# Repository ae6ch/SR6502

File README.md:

# SR6502
Ben Eater style 6502 SBC

Memory Map:  (eventually going to move to a FPGA for mapping)
$0000-$7FFF 32K SRAM (minus 256 Bytes for IO)

$7F00-$7FFF IO

 $7F00 VIA1

 $7F10 ACIA1

$8000-$FFFF 32K EEPROM

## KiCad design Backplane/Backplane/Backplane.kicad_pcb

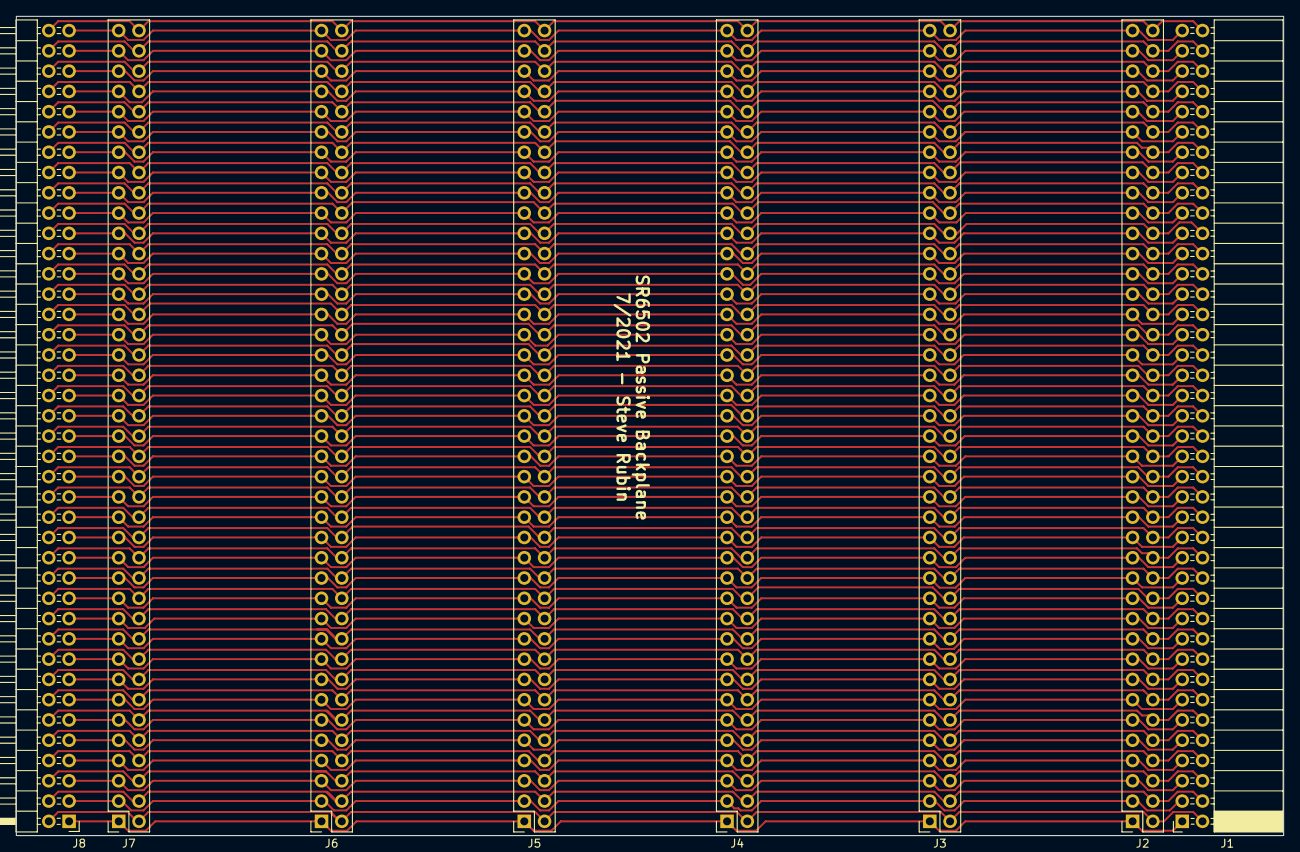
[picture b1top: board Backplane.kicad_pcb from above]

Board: 2 copper layers, 158.8 x 102.6 mm, 8 parts (0 on the bottom side), 80 nets.

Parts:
J1: Conn_02x40_Counter_Clockwise; PinSocket_2x40_P2.54mm_Horizontal
J2, J3, J4, J5, J6, J7: Conn_02x40_Counter_Clockwise; PinSocket_2x40_P2.54mm_Vertical
J8: Conn_02x40_Counter_Clockwise; PinHeader_2x40_P2.54mm_Horizontal

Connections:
/1: J1.1, J2.1, J3.1, J4.1, J5.1, J6.1, J7.1, J8.1
/2: J1.3, J2.3, J3.3, J4.3, J5.3, J6.3, J7.3, J8.3
/3: J1.5, J2.5, J3.5, J4.5, J5.5, J6.5, J7.5, J8.5
/4: J1.7, J2.7, J3.7, J4.7, J5.7, J6.7, J7.7, J8.7
/5: J1.9, J2.9, J3.9, J4.9, J5.9, J6.9, J7.9, J8.9
/6: J1.11, J2.11, J3.11, J4.11, J5.11, J6.11, J7.11, J8.11
/7: J1.13, J2.13, J3.13, J4.13, J5.13, J6.13, J7.13, J8.13
/8: J1.15, J2.15, J3.15, J4.15, J5.15, J6.15, J7.15, J8.15
/9: J1.17, J2.17, J3.17, J4.17, J5.17, J6.17, J7.17, J8.17
/10: J1.19, J2.19, J3.19, J4.19, J5.19, J6.19, J7.19, J8.19
/11: J1.21, J2.21, J3.21, J4.21, J5.21, J6.21, J7.21, J8.21
/12: J1.23, J2.23, J3.23, J4.23, J5.23, J6.23, J7.23, J8.23
/13: J1.25, J2.25, J3.25, J4.25, J5.25, J6.25, J7.25, J8.25
/14: J1.27, J2.27, J3.27, J4.27, J5.27, J6.27, J7.27, J8.27
/15: J1.29, J2.29, J3.29, J4.29, J5.29, J6.29, J7.29, J8.29
/16: J1.31, J2.31, J3.31, J4.31, J5.31, J6.31, J7.31, J8.31
/17: J1.33, J2.33, J3.33, J4.33, J5.33, J6.33, J7.33, J8.33
/18: J1.35, J2.35, J3.35, J4.35, J5.35, J6.35, J7.35, J8.35
/19: J1.37, J2.37, J3.37, J4.37, J5.37, J6.37, J7.37, J8.37
/20: J1.39, J2.39, J3.39, J4.39, J5.39, J6.39, J7.39, J8.39
/21: J1.41, J2.41, J3.41, J4.41, J5.41, J6.41, J7.41, J8.41
/22: J1.43, J2.43, J3.43, J4.43, J5.43, J6.43, J7.43, J8.43
/23: J1.45, J2.45, J3.45, J4.45, J5.45, J6.45, J7.45, J8.45
/24: J1.47, J2.47, J3.47, J4.47, J5.47, J6.47, J7.47, J8.47
/25: J1.49, J2.49, J3.49, J4.49, J5.49, J6.49, J7.49, J8.49
/26: J1.51, J2.51, J3.51, J4.51, J5.51, J6.51, J7.51, J8.51
/27: J1.53, J2.53, J3.53, J4.53, J5.53, J6.53, J7.53, J8.53
/28: J1.55, J2.55, J3.55, J4.55, J5.55, J6.55, J7.55, J8.55
/29: J1.57, J2.57, J3.57, J4.57, J5.57, J6.57, J7.57, J8.57
/30: J1.59, J2.59, J3.59, J4.59, J5.59, J6.59, J7.59, J8.59
/31: J1.61, J2.61, J3.61, J4.61, J5.61, J6.61, J7.61, J8.61
/32: J1.63, J2.63, J3.63, J4.63, J5.63, J6.63, J7.63, J8.63
/33: J1.65, J2.65, J3.65, J4.65, J5.65, J6.65, J7.65, J8.65
/34: J1.67, J2.67, J3.67, J4.67, J5.67, J6.67, J7.67, J8.67
/35: J1.69, J2.69, J3.69, J4.69, J5.69, J6.69, J7.69, J8.69
/36: J1.71, J2.71, J3.71, J4.71, J5.71, J6.71, J7.71, J8.71
/37: J1.73, J2.73, J3.73, J4.73, J5.73, J6.73, J7.73, J8.73
/38: J1.75, J2.75, J3.75, J4.75, J5.75, J6.75, J7.75, J8.75
/39: J1.77, J2.77, J3.77, J4.77, J5.77, J6.77, J7.77, J8.77
/40: J1.79, J2.79, J3.79, J4.79, J5.79, J6.79, J7.79, J8.79
/41: J1.80, J2.80, J3.80, J4.80, J5.80, J6.80, J7.80, J8.80
/42: J1.78, J2.78, J3.78, J4.78, J5.78, J6.78, J7.78, J8.78
/43: J1.76, J2.76, J3.76, J4.76, J5.76, J6.76, J7.76, J8.76
/44: J1.74, J2.74, J3.74, J4.74, J5.74, J6.74, J7.74, J8.74
/45: J1.72, J2.72, J3.72, J4.72, J5.72, J6.72, J7.72, J8.72
/46: J1.70, J2.70, J3.70, J4.70, J5.70, J6.70, J7.70, J8.70
/47: J1.68, J2.68, J3.68, J4.68, J5.68, J6.68, J7.68, J8.68
/48: J1.66, J2.66, J3.66, J4.66, J5.66, J6.66, J7.66, J8.66
/49: J1.64, J2.64, J3.64, J4.64, J5.64, J6.64, J7.64, J8.64
/50: J1.62, J2.62, J3.62, J4.62, J5.62, J6.62, J7.62, J8.62
/51: J1.60, J2.60, J3.60, J4.60, J5.60, J6.60, J7.60, J8.60
/52: J1.58, J2.58, J3.58, J4.58, J5.58, J6.58, J7.58, J8.58
/53: J1.56, J2.56, J3.56, J4.56, J5.56, J6.56, J7.56, J8.56
/54: J1.54, J2.54, J3.54, J4.54, J5.54, J6.54, J7.54, J8.54
/55: J1.52, J2.52, J3.52, J4.52, J5.52, J6.52, J7.52, J8.52
/56: J1.50, J2.50, J3.50, J4.50, J5.50, J6.50, J7.50, J8.50
/57: J1.48, J2.48, J3.48, J4.48, J5.48, J6.48, J7.48, J8.48
/58: J1.46, J2.46, J3.46, J4.46, J5.46, J6.46, J7.46, J8.46
/59: J1.44, J2.44, J3.44, J4.44, J5.44, J6.44, J7.44, J8.44
/60: J1.42, J2.42, J3.42, J4.42, J5.42, J6.42, J7.42, J8.42
/61: J1.40, J2.40, J3.40, J4.40, J5.40, J6.40, J7.40, J8.40
/62: J1.38, J2.38, J3.38, J4.38, J5.38, J6.38, J7.38, J8.38
/63: J1.36, J2.36, J3.36, J4.36, J5.36, J6.36, J7.36, J8.36
/64: J1.34, J2.34, J3.34, J4.34, J5.34, J6.34, J7.34, J8.34
/65: J1.32, J2.32, J3.32, J4.32, J5.32, J6.32, J7.32, J8.32
/66: J1.30, J2.30, J3.30, J4.30, J5.30, J6.30, J7.30, J8.30
/67: J1.28, J2.28, J3.28, J4.28, J5.28, J6.28, J7.28, J8.28
/68: J1.26, J2.26, J3.26, J4.26, J5.26, J6.26, J7.26, J8.26
/69: J1.24, J2.24, J3.24, J4.24, J5.24, J6.24, J7.24, J8.24
/70: J1.22, J2.22, J3.22, J4.22, J5.22, J6.22, J7.22, J8.22
/71: J1.20, J2.20, J3.20, J4.20, J5.20, J6.20, J7.20, J8.20
/72: J1.18, J2.18, J3.18, J4.18, J5.18, J6.18, J7.18, J8.18
/73: J1.16, J2.16, J3.16, J4.16, J5.16, J6.16, J7.16, J8.16
/74: J1.14, J2.14, J3.14, J4.14, J5.14, J6.14, J7.14, J8.14
/75: J1.12, J2.12, J3.12, J4.12, J5.12, J6.12, J7.12, J8.12
/76: J1.10, J2.10, J3.10, J4.10, J5.10, J6.10, J7.10, J8.10
/77: J1.8, J2.8, J3.8, J4.8, J5.8, J6.8, J7.8, J8.8
/78: J1.6, J2.6, J3.6, J4.6, J5.6, J6.6, J7.6, J8.6
/79: J1.4, J2.4, J3.4, J4.4, J5.4, J6.4, J7.4, J8.4
/80: J1.2, J2.2, J3.2, J4.2, J5.2, J6.2, J7.2, J8.2

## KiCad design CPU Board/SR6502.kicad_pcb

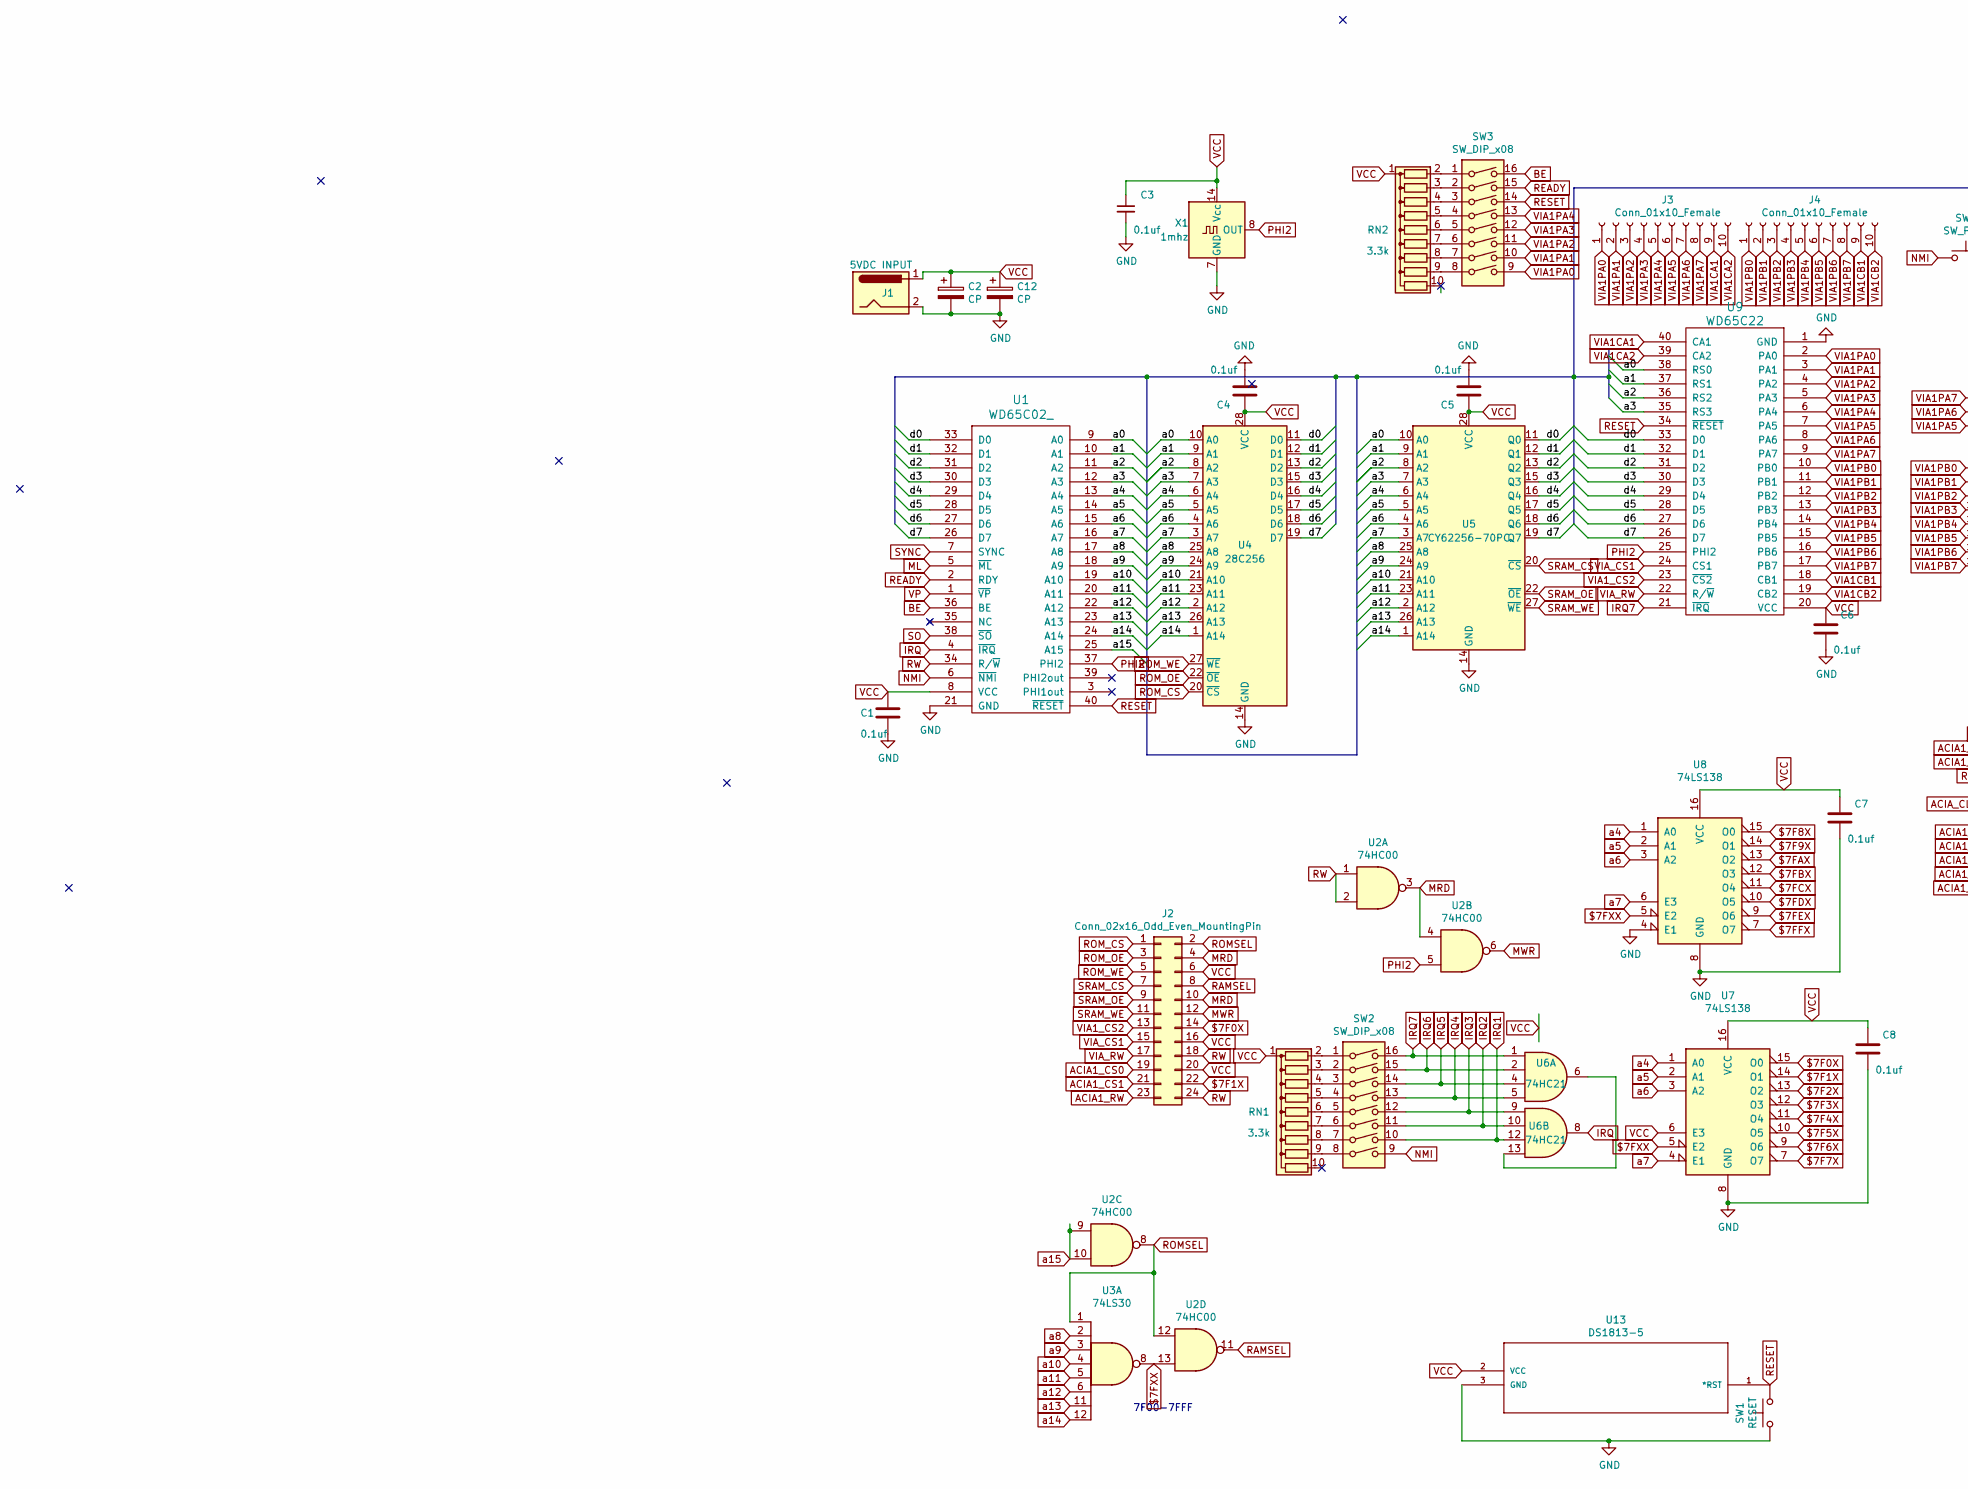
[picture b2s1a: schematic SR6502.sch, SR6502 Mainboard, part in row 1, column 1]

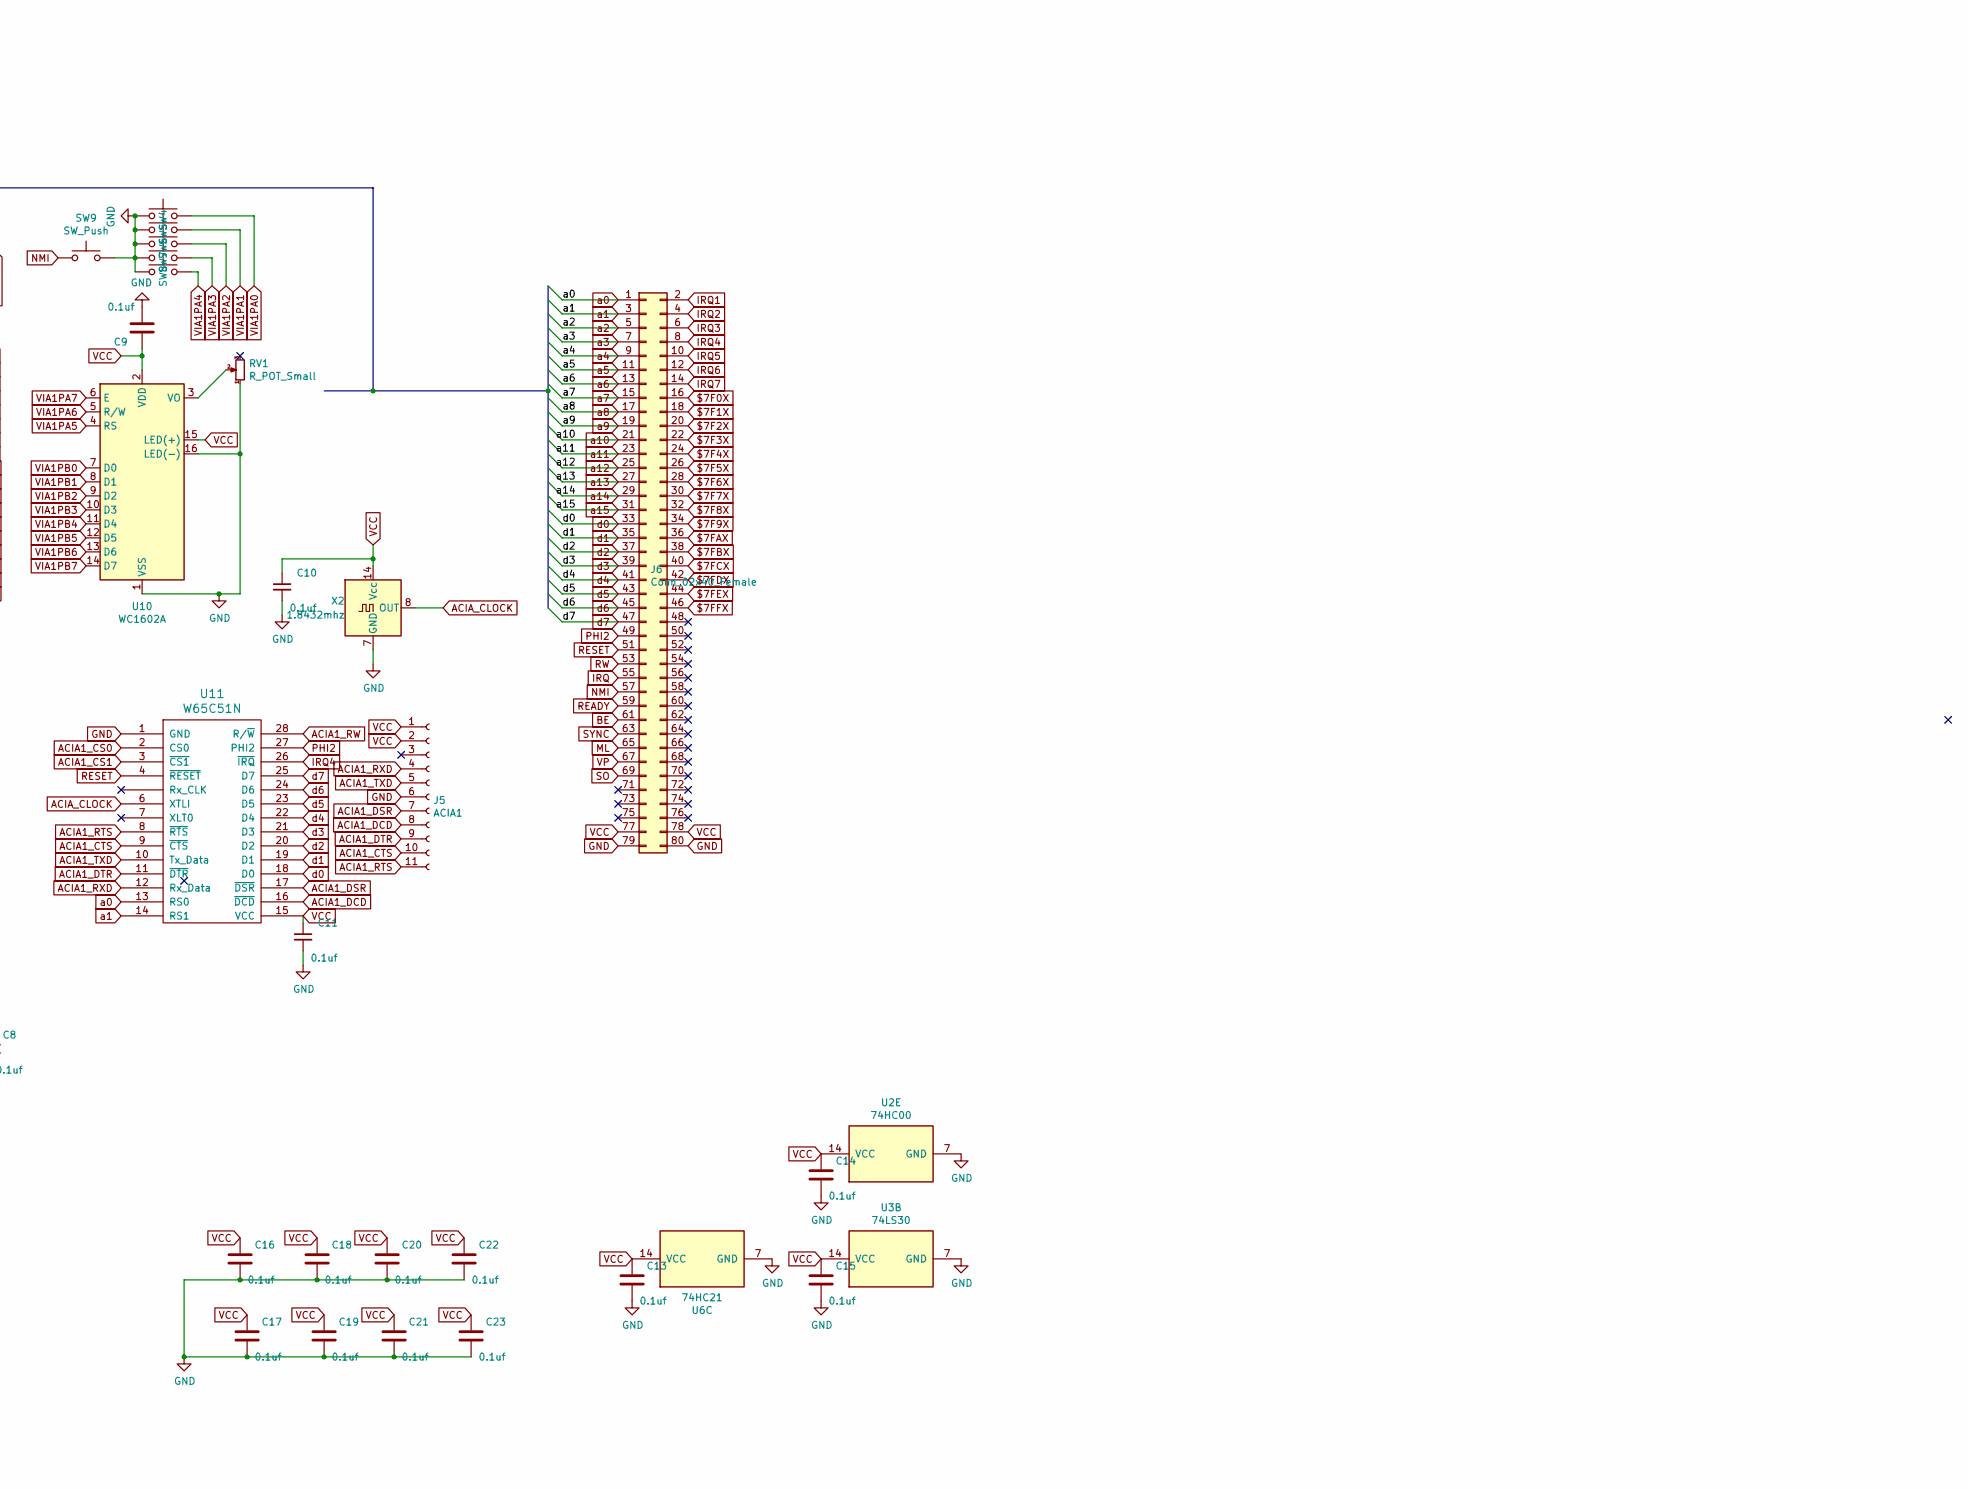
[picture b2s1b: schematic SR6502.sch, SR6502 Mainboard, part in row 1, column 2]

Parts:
C1, C3, C4, C5, C6, C7, C8, C9, C10, C11, C13, C14, C15, C16, C17, C18, C19, C20, C21, C22, C23: 0.1uf; C_Disc_D5.0mm_W2.5mm_P2.50mm
C2, C12: CP; CP_Radial_Tantal_D4.5mm_P2.50mm
J1: 5VDC INPUT; BarrelJack_Horizontal
J2: Conn_02x16_Odd_Even_MountingPin; PinHeader_2x12_P2.54mm_Vertical
J3, J4: Conn_01x10_Female; PinSocket_1x10_P2.54mm_Vertical
J5: ACIA1; PinSocket_1x11_P2.54mm_Vertical
J6: Conn_02x40_Female; PinHeader_2x40_P2.54mm_Horizontal
RN1, RN2: 3.3k; R_Array_SIP10
RV1: R_POT_Small; Potentiometer_Vishay_T73XW_Horizontal
SW1: RESET; SW_Tactile_Straight_KSA0Axx1LFTR
SW2, SW3: SW_DIP_x08; SW_DIP_SPSTx08_Slide_9.78x22.5mm_W7.62mm_P2.54mm
SW4, SW5, SW6, SW7, SW8, SW9: SW_Push; SW_Tactile_Straight_KSA0Axx1LFTR
U1: WD65C02_; DIP-40_W15.24mm_Socket
U2: 74HC00; DIP-14_W7.62mm_Socket
U3: 74LS30; DIP-14_W7.62mm_Socket
U4: 28C256; DIP-28_W15.24mm_Socket
U5: CY62256-70PC; DIP-28_W15.24mm_Socket
U6: 74HC21; DIP-14_W7.62mm_Socket
U7, U8: 74LS138; DIP-16_W7.62mm_Socket
U9: WD65C22; DIP-40_W15.24mm_Socket
U10: WC1602A
U11: W65C51N; DIP-28_W15.24mm
U13: DS1813-5; TO-92_Inline; MANUFACTURER_PART_NUMBER ds18135+
X1: 1mhz; Oscillator_DIP-14
X2: 1.8432mhz; Oscillator_DIP-14

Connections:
$7F0X: J2.14, J6.16, U7.15 (O0)
$7F1X: J2.22, J6.18, U7.14 (O1)
$7F2X: J6.20, U7.13 (O2)
$7F3X: J6.22, U7.12 (O3)
$7F4X: J6.24, U7.11 (O4)
$7F5X: J6.26, U7.10 (O5)
$7F6X: J6.28, U7.9 (O6)
$7F7X: J6.30, U7.7 (O7)
$7F8X: J6.32, U8.15 (O0)
$7F9X: J6.34, U8.14 (O1)
$7FAX: J6.36, U8.13 (O2)
$7FBX: J6.38, U8.12 (O3)
$7FCX: J6.40, U8.11 (O4)
$7FDX: J6.42, U8.10 (O5)
$7FEX: J6.44, U8.9 (O6)
$7FFX: J6.46, U8.7 (O7)
$7FXX: U2.13, U3.8, U7.5 (E2), U8.5 (E2)
ACIA1_CS0: J2.19, U11.2 (CS0)
ACIA1_CS1: J2.21, U11.3 (~CS1)
ACIA1_CTS: J5.10, U11.9 (~CTS)
ACIA1_DCD: J5.8, U11.16 (~DCD)
ACIA1_DSR: J5.7, U11.17 (~DSR)
ACIA1_DTR: J5.9, U11.11 (~DTR)
ACIA1_RTS: J5.11, U11.8 (~RTS)
ACIA1_RW: J2.23, U11.28 (R/~W)
ACIA1_RXD: J5.4, U11.12 (Rx_Data)
ACIA1_TXD: J5.5, U11.10 (Tx_Data)
ACIA_CLOCK: U11.6 (XTLI), X2.8 (OUT)
BE: J6.61, SW3.16, U1.36 (BE)
GND: C1.2, C2.2, C3.2, C4.2, C5.2, C6.2, C7.2, C8.2, C9.2, C10.2, C11.2, C12.2, C13.2, C14.2, C15.2, C16.2, C17.2, C18.2, C19.2, C20.2, C21.2, C22.2, C23.2, J1.2, J5.6, J6.79, J6.80, RV1.1, SW1.1, SW4.1, SW5.1, SW6.1, SW7.1, SW8.1, SW9.2, U1.21 (GND), U2.7 (GND), U3.7 (GND), U4.14 (GND), U5.14 (GND), U6.7 (GND), U7.8 (GND), U8.4 (E1), U8.8 (GND), U9.1 (GND), U10.1 (VSS), U10.16 (LED(-)), U11.1 (GND), U13.3 (GND), X1.7 (GND), X2.7 (GND)
IRQ: J6.55, U1.4 (~IRQ), U6.8
IRQ1: J6.2, SW2.10, U6.12
IRQ2: J6.4, SW2.11, U6.10
IRQ3: J6.6, SW2.12, U6.9
IRQ4: J6.8, SW2.13, U6.5, U11.26 (~IRQ)
IRQ5: J6.10, SW2.14, U6.4
IRQ6: J6.12, SW2.15, U6.2
IRQ7: J6.14, SW2.16, U6.1, U9.21 (~IRQ)
ML: J6.65, U1.5 (~ML)
MRD: J2.4, J2.10, U2.3, U2.4
MWR: J2.12, U2.6
NMI: J6.57, SW2.9, SW9.1, U1.6 (~NMI)
unnamed: RN1.2 (R1), SW2.1
unnamed: RN1.3 (R2), SW2.2
unnamed: RN1.4 (R3), SW2.3
unnamed: RN1.5 (R4), SW2.4
unnamed: RN1.6 (R5), SW2.5
unnamed: RN1.7 (R6), SW2.6
unnamed: RN1.8 (R7), SW2.7
unnamed: RN1.9 (R8), SW2.8
unnamed: RN2.2 (R1), SW3.1
unnamed: RN2.3 (R2), SW3.2
unnamed: RN2.4 (R3), SW3.3
unnamed: RN2.5 (R4), SW3.4
unnamed: RN2.6 (R5), SW3.5
unnamed: RN2.7 (R6), SW3.6
unnamed: RN2.8 (R7), SW3.7
unnamed: RN2.9 (R8), SW3.8
unnamed: RV1.2, U10.3 (VO)
unnamed: U6.6, U6.13
PHI2: J6.49, U1.37 (PHI2), U2.5, U9.25 (PHI2), U11.27 (PHI2), X1.8 (OUT)
RAMSEL: J2.8, U2.11
READY: J6.59, SW3.15, U1.2 (RDY)
RESET: J6.51, SW1.2, SW3.14, U1.40 (~RESET), U9.34 (~RESET), U11.4 (~RESET), U13.1 (*RST)
ROMSEL: J2.2, U2.8, U2.12, U3.1
ROM_CS: J2.1, U4.20 (~CS)
ROM_OE: J2.3, U4.22 (~OE)
ROM_WE: J2.5, U4.27 (~WE)
RW: J2.18, J2.24, J6.53, U1.34 (R/~W), U2.1, U2.2
SO: J6.69, U1.38 (~SO)
SRAM_CS: J2.7, U5.20 (~CS)
SRAM_OE: J2.9, U5.22 (~OE)
SRAM_WE: J2.11, U5.27 (~WE)
SYNC: J6.63, U1.7 (SYNC)
VCC: C1.1, C2.1, C3.1, C4.1, C5.1, C6.1, C7.1, C8.1, C9.1, C10.1, C11.1, C12.1, C13.1, C14.1, C15.1, C16.1, C17.1, C18.1, C19.1, C20.1, C21.1, C22.1, C23.1, J1.1, J2.6, J2.16, J2.20, J5.1, J5.2, J6.77, J6.78, RN1.1 (common), RN2.1 (common), U1.8 (VCC), U2.14 (VCC), U3.14 (VCC), U4.28 (VCC), U5.28 (VCC), U6.14 (VCC), U7.6 (E3), U7.16 (VCC), U8.16 (VCC), U9.20 (VCC), U10.2 (VDD), U10.15 (LED(+)), U11.15 (VCC), U13.2 (VCC), X1.14 (Vcc), X2.14 (Vcc)
VIA1CA1: J3.9, U9.40 (CA1)
VIA1CA2: J3.10, U9.39 (CA2)
VIA1CB1: J4.9, U9.18 (CB1)
VIA1CB2: J4.10, U9.19 (CB2)
VIA1PA0: J3.1, SW3.9, SW4.2, U9.2 (PA0)
VIA1PA1: J3.2, SW3.10, SW5.2, U9.3 (PA1)
VIA1PA2: J3.3, SW3.11, SW6.2, U9.4 (PA2)
VIA1PA3: J3.4, SW3.12, SW7.2, U9.5 (PA3)
VIA1PA4: J3.5, SW3.13, SW8.2, U9.6 (PA4)
VIA1PA5: J3.6, U9.7 (PA5), U10.4 (RS)
VIA1PA6: J3.7, U9.8 (PA6), U10.5 (R/W)
VIA1PA7: J3.8, U9.9 (PA7), U10.6 (E)
VIA1PB0: J4.1, U9.10 (PB0), U10.7 (D0)
VIA1PB1: J4.2, U9.11 (PB1), U10.8 (D1)
VIA1PB2: J4.3, U9.12 (PB2), U10.9 (D2)
VIA1PB3: J4.4, U9.13 (PB3), U10.10 (D3)
VIA1PB4: J4.5, U9.14 (PB4), U10.11 (D4)
VIA1PB5: J4.6, U9.15 (PB5), U10.12 (D5)
VIA1PB6: J4.7, U9.16 (PB6), U10.13 (D6)
VIA1PB7: J4.8, U9.17 (PB7), U10.14 (D7)
VIA1_CS2: J2.13, U9.23 (~CS2)
VIA_CS1: J2.15, U9.24 (CS1)
VIA_RW: J2.17, U9.22 (R/~W)
VP: J6.67, U1.1 (~VP)
a0: J6.1, U1.9 (A0), U4.10 (A0), U5.10 (A0), U9.38 (RS0), U11.13 (RS0)
a1: J6.3, U1.10 (A1), U4.9 (A1), U5.9 (A1), U9.37 (RS1), U11.14 (RS1)
a2: J6.5, U1.11 (A2), U4.8 (A2), U5.8 (A2), U9.36 (RS2)
a3: J6.7, U1.12 (A3), U4.7 (A3), U5.7 (A3), U9.35 (RS3)
a4: J6.9, U1.13 (A4), U4.6 (A4), U5.6 (A4), U7.1 (A0), U8.1 (A0)
a5: J6.11, U1.14 (A5), U4.5 (A5), U5.5 (A5), U7.2 (A1), U8.2 (A1)
a6: J6.13, U1.15 (A6), U4.4 (A6), U5.4 (A6), U7.3 (A2), U8.3 (A2)
a7: J6.15, U1.16 (A7), U4.3 (A7), U5.3 (A7), U7.4 (E1), U8.6 (E3)
a8: J6.17, U1.17 (A8), U3.2, U4.25 (A8), U5.25 (A8)
a9: J6.19, U1.18 (A9), U3.3, U4.24 (A9), U5.24 (A9)
a10: J6.21, U1.19 (A10), U3.4, U4.21 (A10), U5.21 (A10)
a11: J6.23, U1.20 (A11), U3.5, U4.23 (A11), U5.23 (A11)
a12: J6.25, U1.22 (A12), U3.6, U4.2 (A12), U5.2 (A12)
a13: J6.27, U1.23 (A13), U3.11, U4.26 (A13), U5.26 (A13)
a14: J6.29, U1.24 (A14), U3.12, U4.1 (A14), U5.1 (A14)
a15: J6.31, U1.25 (A15), U2.9, U2.10
d0: J6.33, U1.33 (D0), U4.11 (D0), U5.11 (Q0), U9.33 (D0), U11.18 (D0)
d1: J6.35, U1.32 (D1), U4.12 (D1), U5.12 (Q1), U9.32 (D1), U11.19 (D1)
d2: J6.37, U1.31 (D2), U4.13 (D2), U5.13 (Q2), U9.31 (D2), U11.20 (D2)
d3: J6.39, U1.30 (D3), U4.15 (D3), U5.15 (Q3), U9.30 (D3), U11.21 (D3)
d4: J6.41, U1.29 (D4), U4.16 (D4), U5.16 (Q4), U9.29 (D4), U11.22 (D4)
d5: J6.43, U1.28 (D5), U4.17 (D5), U5.17 (Q5), U9.28 (D5), U11.23 (D5)
d6: J6.45, U1.27 (D6), U4.18 (D6), U5.18 (Q6), U9.27 (D6), U11.24 (D6)
d7: J6.47, U1.26 (D7), U4.19 (D7), U5.19 (Q7), U9.26 (D7), U11.25 (D7)

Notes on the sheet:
7F00-7FFF

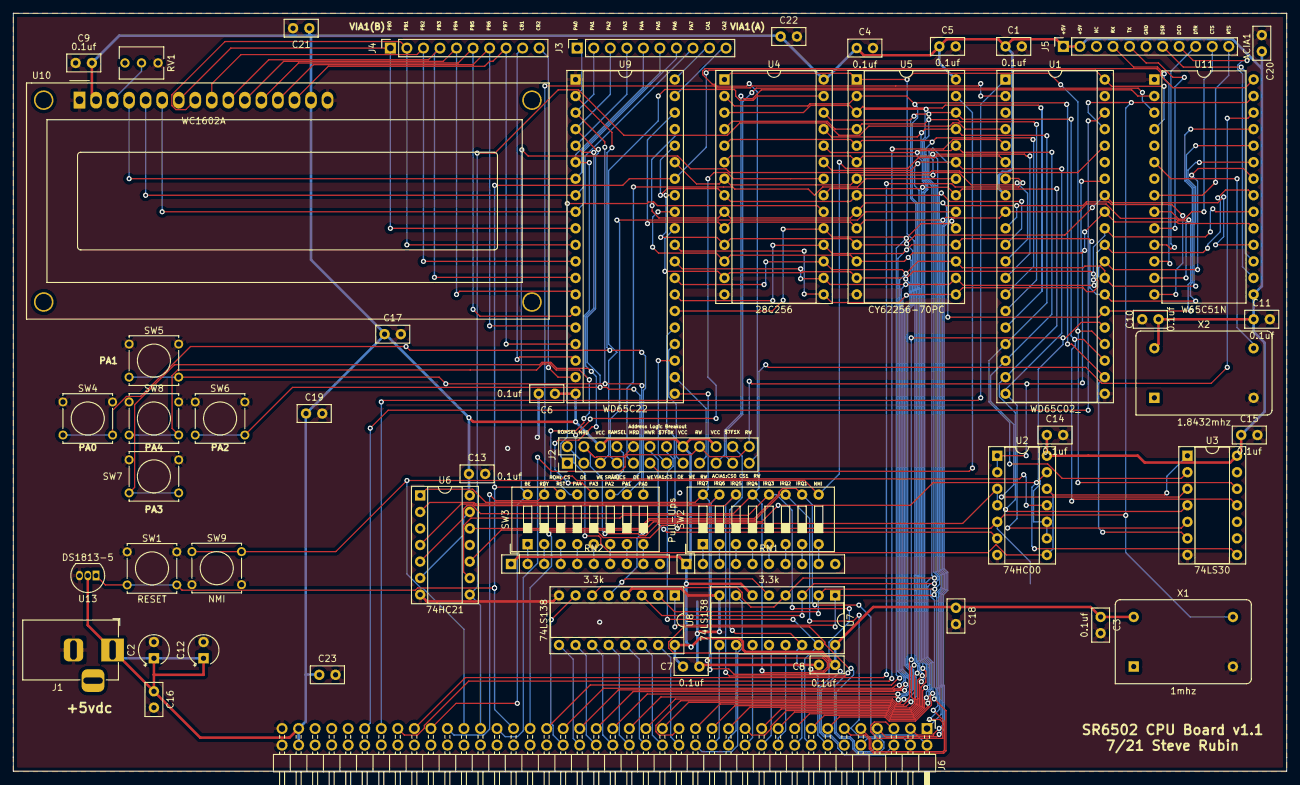
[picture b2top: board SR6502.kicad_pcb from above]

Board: 2 copper layers, 195.6 x 116.4 mm, 55 parts (0 on the bottom side), 123 nets.

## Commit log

2021-06-16 Add files via upload
    Initial Commit
2021-06-16 added vectors.s
2021-06-17 Minor changes
2021-06-17 modified readme
2021-06-21 Updated memory map, starting working on serial console
2021-06-29 fixed errors in schematic (5 missing traces on pcb), did not export gerber yet
2021-07-06 changed memory map, added ACIA and 2nd VIA, irq matrix, added backplane pcb
2021-07-22 Final push to JLCPCB for latest rev
